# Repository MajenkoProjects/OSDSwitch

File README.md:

# OSDSwitch
FF-OSD Video Switcher for clean video output

This is a small board with a high bandwidth video switching chip
on it. The idea is that this sits in between the video generation 
circuitry and the video output socket of your Amiga (or similar
computer) and is controlled by the On Screen Display signal from
a modified Gotek (see [keirf/flashfloppy-osd](https://github.com/keirf/flashfloppy-osd).

Normally the output of the OSD mod is just blasted unceremoniously
over the green (or channel of your choice) signal, overpowering the
circuitry in the receiving display system to give a green tint where
the text is.

This is not great. It's crude, and doesn't always work right, and
the results are often less than desirable. 

This small board is the answer. It actively cuts out the normal
video signal when the OSD text should be displayed, and replaces that
video signal with a statically defined colour of your choice (configured
by 3 jumpers) to give a crystal clear OSD that is embedded within the
video stream, not overlayed on top of it.

I developed this board because I use an Extron video scaler connected
to my Amiga for both video capture while livestreaming and for display
on a modern TFT screen. But the traditional overlay setup really didn't
work with the Extron.  Everything went pink:

And so this board was born. The ADG1633BCPZ looked to be the ideal
chip, with more than enough bandwidth for a video signal (one of the
intended applications for this chip), and three channels, the board
was pretty simple to design. And I think you'll agree the results
are much nicer:

(This image is from before I tweaked the resistor values a little,
so the OSD is a bit darker than I would have liked).

Installation is reasonably simple. For the Amiga 500 (R6):

* Lift the side of the three ferrite beads by the video connector that is facing
  towards Denise (where you would normally solder the OSD wire to.
* Connect three wires to where they were soldered
* Attach the three wires to the INPUT side of the board's R G and B pins.
* Solder the ferrite beads you just lifted one side of to the output
  R G and B pins
* Connect a 5V and GND signal from somewhere suitable
* Connect the signal from your OSD generator to the IN pin.

Choose the colour you want with the jumpers (bonus hack: if you use resistors
instead of jumpers you can get a wider range of colours to choose from).

And here it is installed in my Amiga:

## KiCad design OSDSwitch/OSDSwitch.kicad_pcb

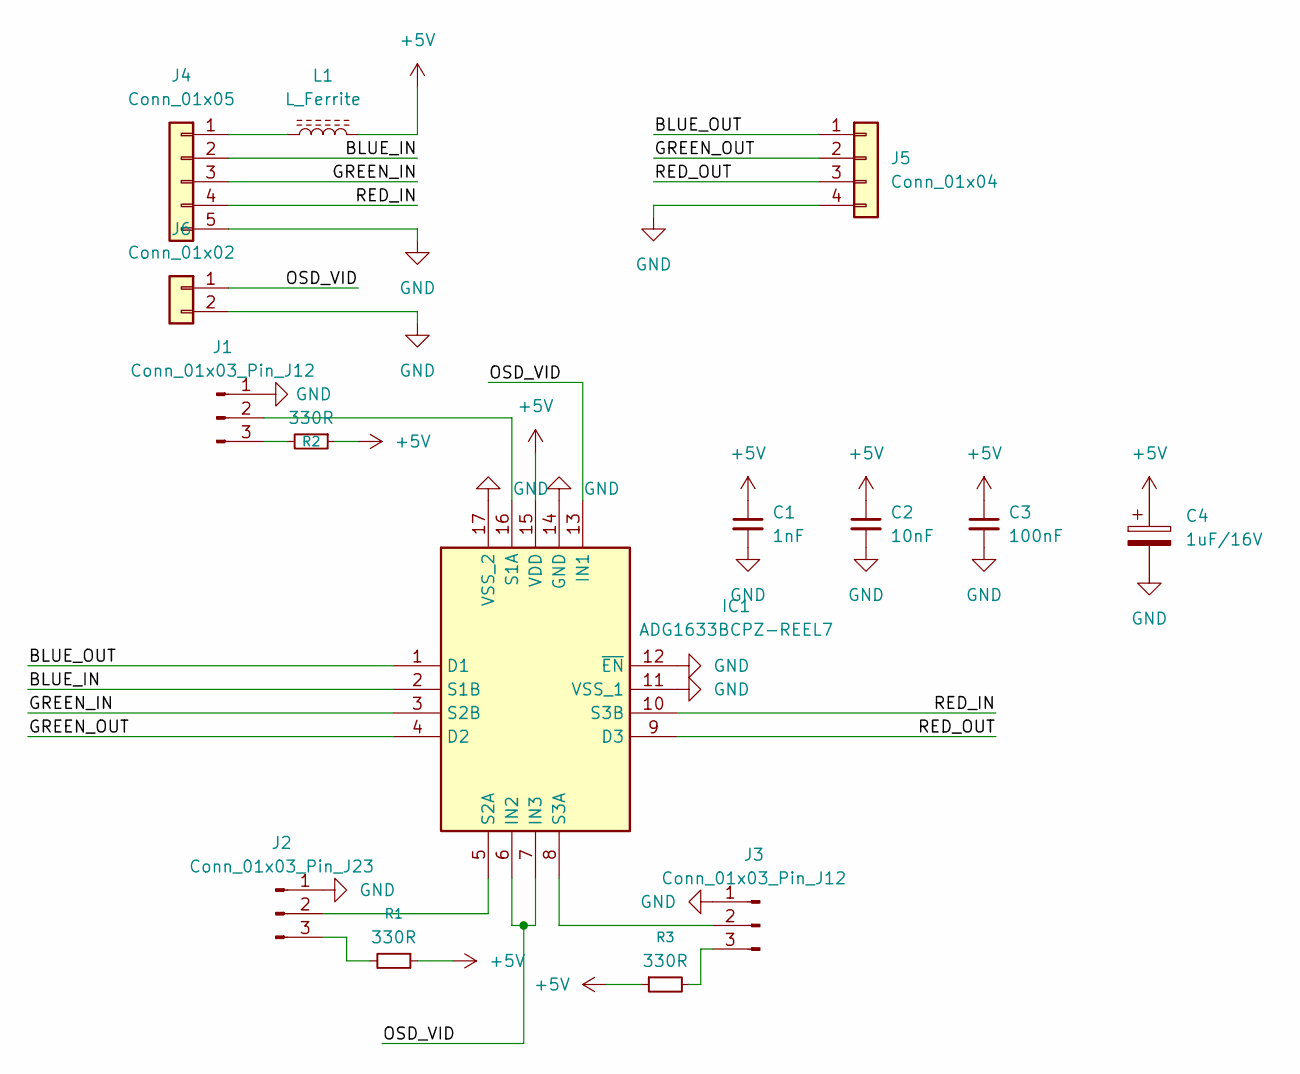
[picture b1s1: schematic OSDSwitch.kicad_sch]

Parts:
C1: 1nF; C_0402_1005Metric
C2: 10nF; C_0402_1005Metric
C3: 100nF; C_0402_1005Metric
C4: 1uF/16V; CP_Elec_4x5.4
IC1: ADG1633BCPZ-REEL7; QFN-16-1EP_3x3mm_P0.5mm_EP1.75x1.75mm; Mouser Part Number 584-ADG1633BCPZ-R7
J1, J3: Conn_01x03_Pin_J12; PinHeader_1x03_P2.54mm_Vertical
J2: Conn_01x03_Pin_J23; PinHeader_1x03_P2.54mm_Vertical
J4: Conn_01x05; PinHeader_1x05_P2.54mm_Vertical
J5: Conn_01x04; PinHeader_1x04_P2.54mm_Vertical
J6: Conn_01x02; PinHeader_1x02_P2.54mm_Vertical
L1: L_Ferrite; L_0603_1608Metric
R1, R2, R3: 330R; R_0402_1005Metric

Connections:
+5V: C1.1, C2.1, C3.1, C4.1, IC1.15 (VDD), L1.2, R1.1, R2.1, R3.1
/BLUE_IN: IC1.2 (S1B), J4.2
/BLUE_OUT: IC1.1 (D1), J5.1
/GREEN_IN: IC1.3 (S2B), J4.3
/GREEN_OUT: IC1.4 (D2), J5.2
/OSD_VID: IC1.6 (IN2), IC1.7 (IN3), IC1.13 (IN1), J6.1
/RED_IN: IC1.10 (S3B), J4.4
/RED_OUT: IC1.9 (D3), J5.3
GND: C1.2, C2.2, C3.2, C4.2, IC1.11 (VSS_1), IC1.12 (~EN), IC1.14 (GND), IC1.17 (VSS_2), J1.1, J2.1, J3.1, J4.5, J5.4, J6.2
unnamed: IC1.16 (S1A), J1.2
unnamed: IC1.5 (S2A), J2.2
unnamed: IC1.8 (S3A), J3.2
unnamed: J1.3, R2.2
unnamed: J2.3, R1.2
unnamed: J3.3, R3.2
unnamed: J4.1, L1.1

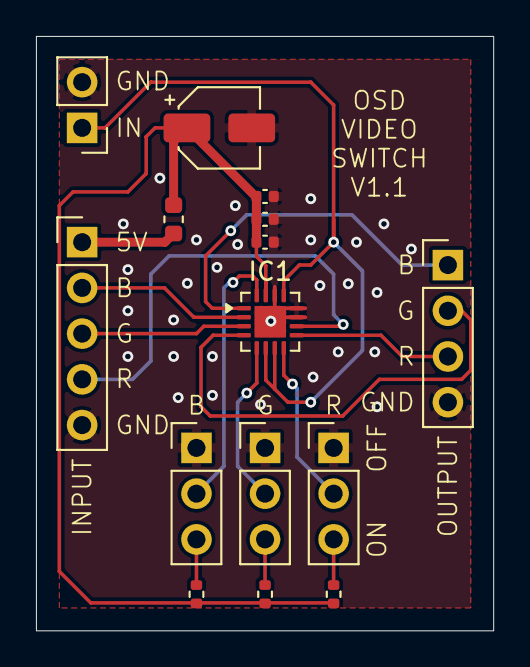
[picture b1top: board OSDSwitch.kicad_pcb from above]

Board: 2 copper layers, 25.4 x 33.0 mm, 15 parts (0 on the bottom side), 16 nets.

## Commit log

2026-02-18 Initial import
2026-02-18 Added PDF
2026-03-27 Corrected chip footprint
2026-03-27 Swapped red and blue to match Amiga 500 video output order
2026-03-28 Added writeup
2026-03-28 Updated PDF
